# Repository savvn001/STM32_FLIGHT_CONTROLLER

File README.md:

# STM32_FLIGHT_CONTROLLER

(Still undergoing active development)

Open source flight controller running on an STM32F411RE MCU and a custom designed PCB. Project written in STM32cubeIDE. 

The other modules this flight controller currently uses:

- NRF24L01PA for RF comms
- GPS is provided by a uBlox NEO6M GPS module
- Orientation from an MPU9250 9-axis IMU.

Current features:
- User control
- Packetised RF communications
- GPS 
- In flight monitoring of telemetry information (battery level, orientation, GPS co-ordinates etc.)
- More to come!

The first revision of the flight controller designed in eagle is shown below.

The controller features headers for I2C, 4 GPIO pins, UART and an NRF24L01 module. The code for the associated user controller/transmitter is here: https://github.com/savvn001/DRONE_CONTROLLER_F4746NG

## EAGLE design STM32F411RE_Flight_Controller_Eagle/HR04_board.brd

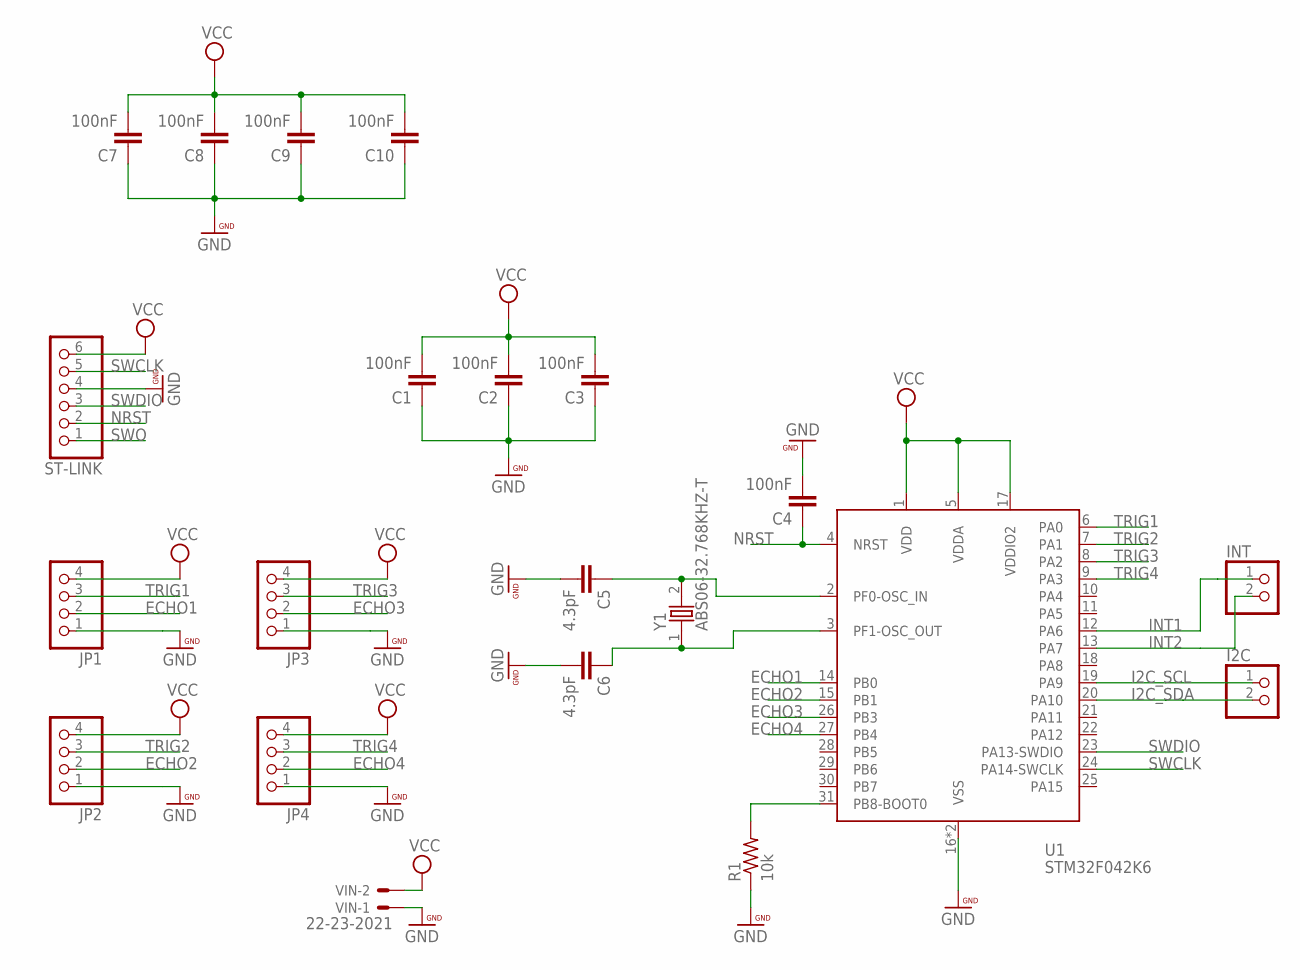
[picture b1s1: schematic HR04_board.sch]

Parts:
C1, C2, C3, C4, C7, C8, C9, C10: 100nF; 0603-CAP
C5, C6: 4.3pF; 0402-CAP
I2C: PINHD-1X2; 1X02
INT: PINHD-1X2; 1X02
JP1, JP2, JP3, JP4: PINHD-1X4; 1X04
R1: 10k; R0603
ST-LINK: PINHD-1X6; 1X06
U1: STM32F042K6; QFP32-7X7
VIN: 22-23-2021
Y1: ABS06-32.768KHZ-T; XTAL_ABS06-32.768KHZ-T

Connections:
ECHO1: JP1.2, U1.14 (PB0)
ECHO2: JP2.2, U1.15 (PB1)
ECHO3: JP3.2, U1.26 (PB3)
ECHO4: JP4.2, U1.27 (PB4)
GND: C1.1, C2.1, C3.1, C4.2, C5.2, C6.2, C7.1, C8.1, C9.1, C10.1, JP1.1, JP2.1, JP3.1, JP4.1, R1.1, ST-LINK.4, U1.16 (VSS), U1.32 (VSS), VIN.1
I2C_SCL: I2C.1, U1.19 (PA9)
I2C_SDA: I2C.2, U1.20 (PA10)
INT1: INT.1, U1.12 (PA6)
INT2: INT.2, U1.13 (PA7)
unnamed: R1.2, U1.31 (PB8-BOOT0)
unnamed: C5.1, U1.2 (PF0-OSC_IN), Y1.2
unnamed: C6.1, U1.3 (PF1-OSC_OUT), Y1.1
NRST: C4.1, ST-LINK.2, U1.4 (NRST)
SWCLK: ST-LINK.5, U1.24 (PA14-SWCLK)
SWDIO: ST-LINK.3, U1.23 (PA13-SWDIO)
SWO: ST-LINK.1
TRIG1: JP1.3, U1.6 (PA0)
TRIG2: JP2.3, U1.7 (PA1)
TRIG3: JP3.3, U1.8 (PA2)
TRIG4: JP4.3, U1.9 (PA3)
VCC: C1.2, C2.2, C3.2, C7.2, C8.2, C9.2, C10.2, JP1.4, JP2.4, JP3.4, JP4.4, ST-LINK.6, U1.1 (VDD), U1.5 (VDDA), U1.17 (VDDIO2), VIN.2

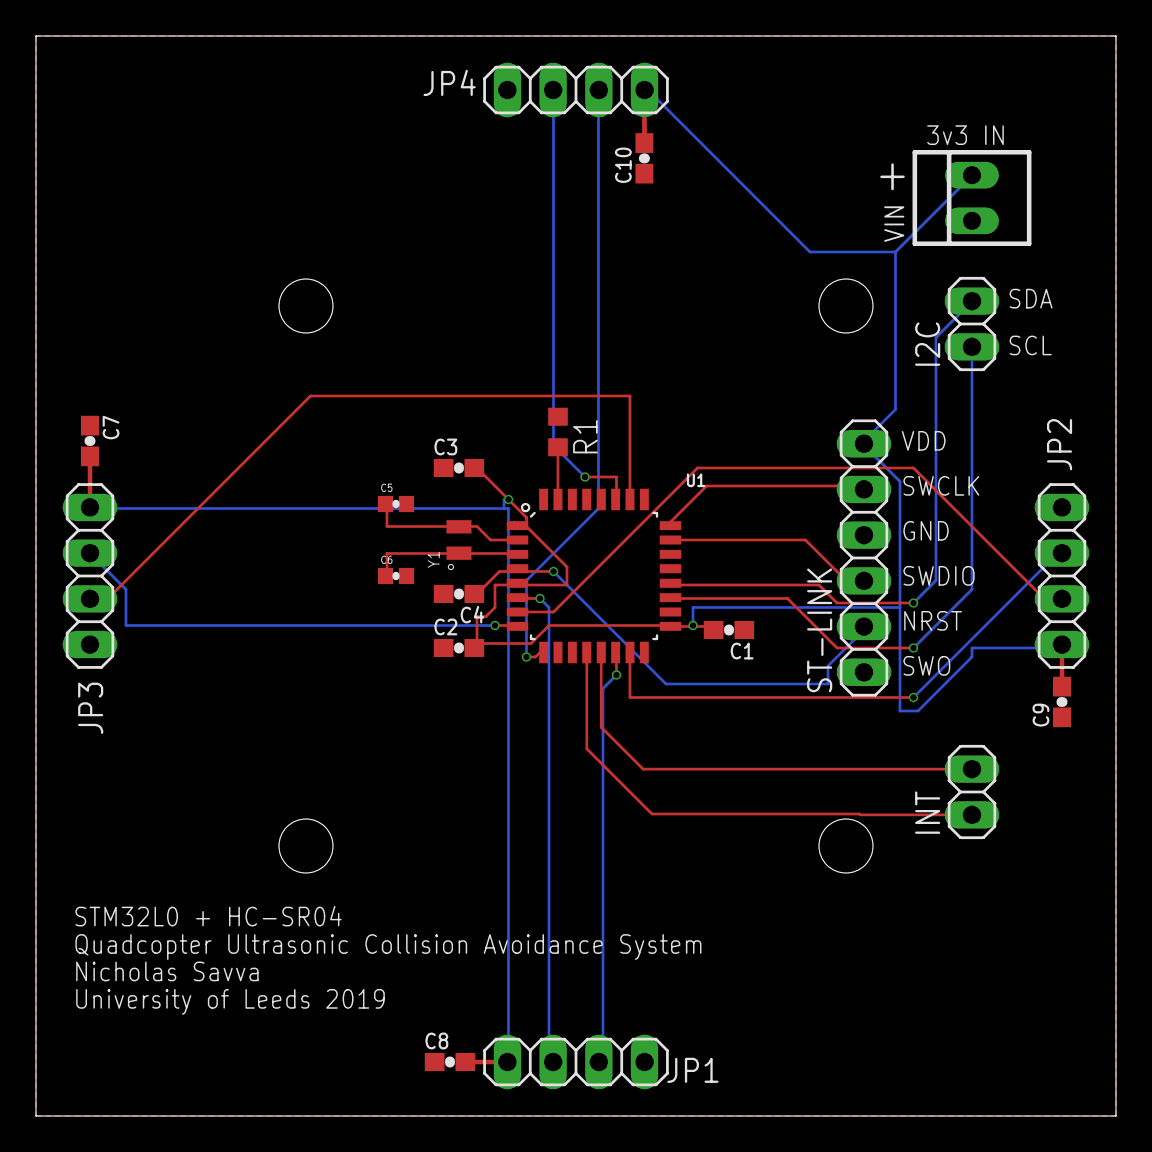
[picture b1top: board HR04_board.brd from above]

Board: 2 copper layers, 60.0 x 60.0 mm, 21 parts (0 on the bottom side), 20 nets.

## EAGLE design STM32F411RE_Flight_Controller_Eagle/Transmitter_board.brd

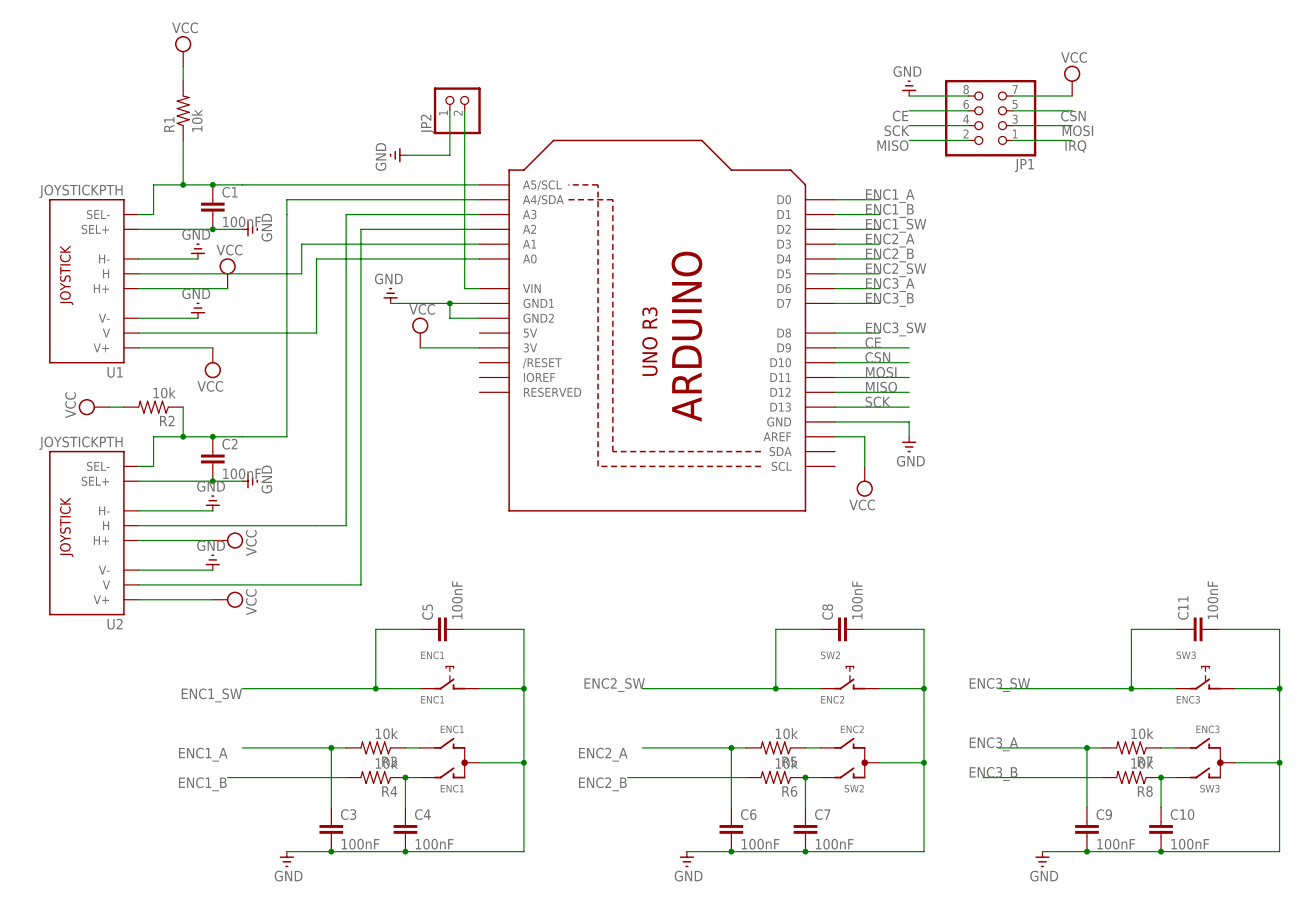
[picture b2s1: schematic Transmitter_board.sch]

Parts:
C1, C2, C3, C4, C5, C6, C7, C8, C9, C10, C11: 100nF; 0603-CAP
ENC1: ENC1; ALPS_EC12E_SW
JP1: PINHD-2X4; 2X04
JP2: PINHD-1X2; 1X02
R1, R2, R3, R4, R5, R6, R7, R8: 10k; 0603-RES
SW2: ENC2; ALPS_EC12E_SW
SW3: ENC3; ALPS_EC12E_SW
U1, U2: JOYSTICKPTH; JOYSTICK
U3: STM32F746NG; ARDUINOR3-BPLACE

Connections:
5V: U3.5V
CE: JP1.6, U3.D9
CSN: JP1.5, U3.D10
ENC1_A: C3.1, R3.2, U3.D0
ENC1_B: R4.2, U3.D1
ENC1_SW: C5.1, ENC1.E (2), U3.D2
ENC2_A: C6.1, R5.2, U3.D3
ENC2_B: R6.2, U3.D4
ENC2_SW: C8.1, SW2.E (2), U3.D5
ENC3_A: C9.1, R7.2, U3.D6
ENC3_B: R8.2, U3.D7
ENC3_SW: C11.1, SW3.E (2), U3.D8
GND: C1.2, C2.2, C3.2, C4.2, C5.2, C6.2, C7.2, C8.2, C9.2, C10.2, C11.2, ENC1.C, ENC1.D (1), JP1.8, JP2.1, SW2.C, SW2.D (1), SW3.C, SW3.D (1), U1.B1A (SEL+), U1.H3 (H-), U1.V3 (V-), U2.B1A (SEL+), U2.H3 (H-), U2.V3 (V-), U3.GND, U3.GND1, U3.GND2
IRQ: JP1.1
MISO: JP1.2, U3.D12
MOSI: JP1.3, U3.D11
unnamed: U2.V2 (V), U3.A2
unnamed: C2.1, R2.1, U2.B2A (SEL-), U3.A4 (A4/SDA)
unnamed: JP2.2, U3.VIN
unnamed: C1.1, R1.1, U1.B2A (SEL-), U3.A5 (A5/SCL)
unnamed: C4.1, ENC1.A, R4.1
unnamed: C7.1, R6.1, SW2.A
unnamed: ENC1.B, R3.1
unnamed: R5.1, SW2.B
unnamed: C10.1, R8.1, SW3.A
unnamed: R7.1, SW3.B
unnamed: U1.H2 (H), U3.A1
unnamed: U1.V2 (V), U3.A0
unnamed: U2.H2 (H), U3.A3
SCK: JP1.4, U3.D13
VCC: JP1.7, R1.2, R2.2, U1.H1 (H+), U1.V1 (V+), U2.H1 (H+), U2.V1 (V+), U3.3V, U3.AREF

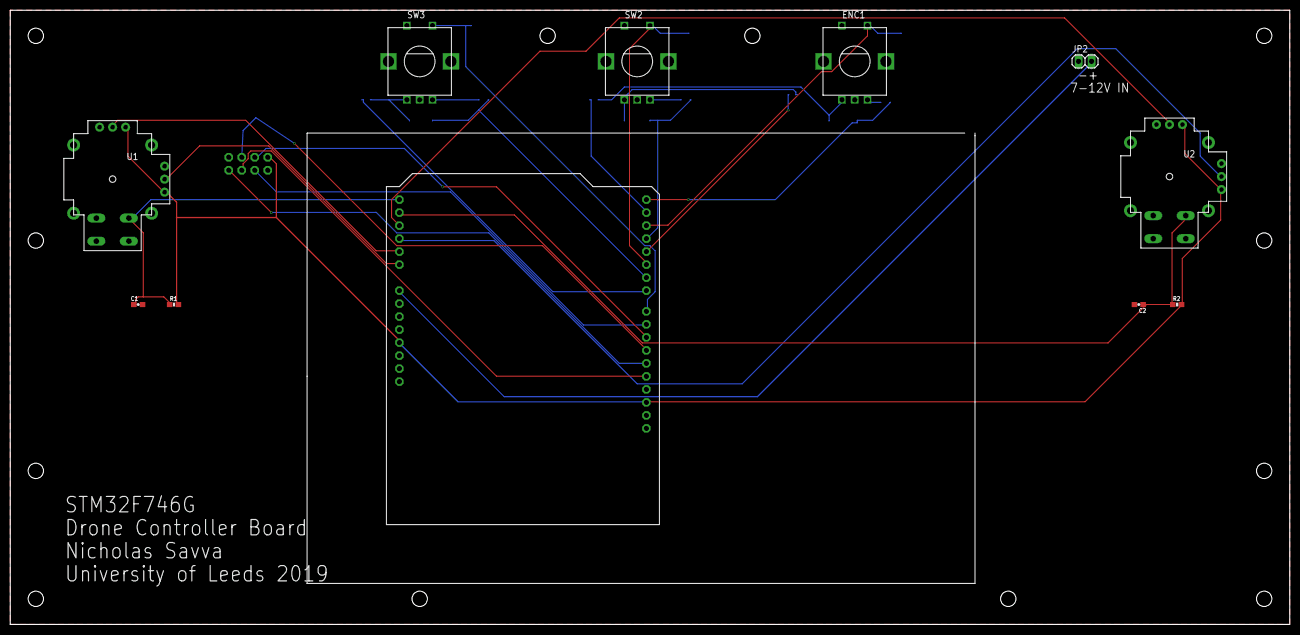
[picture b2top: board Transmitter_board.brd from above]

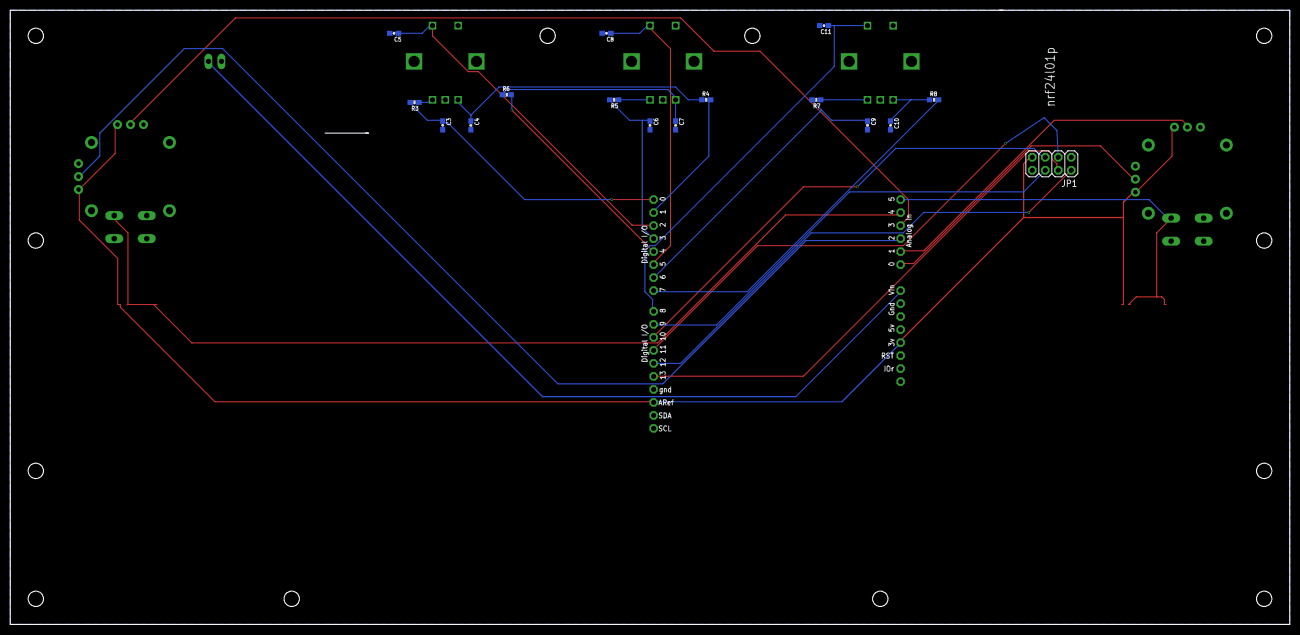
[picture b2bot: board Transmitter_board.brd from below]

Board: 2 copper layers, 250.0 x 120.0 mm, 27 parts (17 on the bottom side), 29 nets.

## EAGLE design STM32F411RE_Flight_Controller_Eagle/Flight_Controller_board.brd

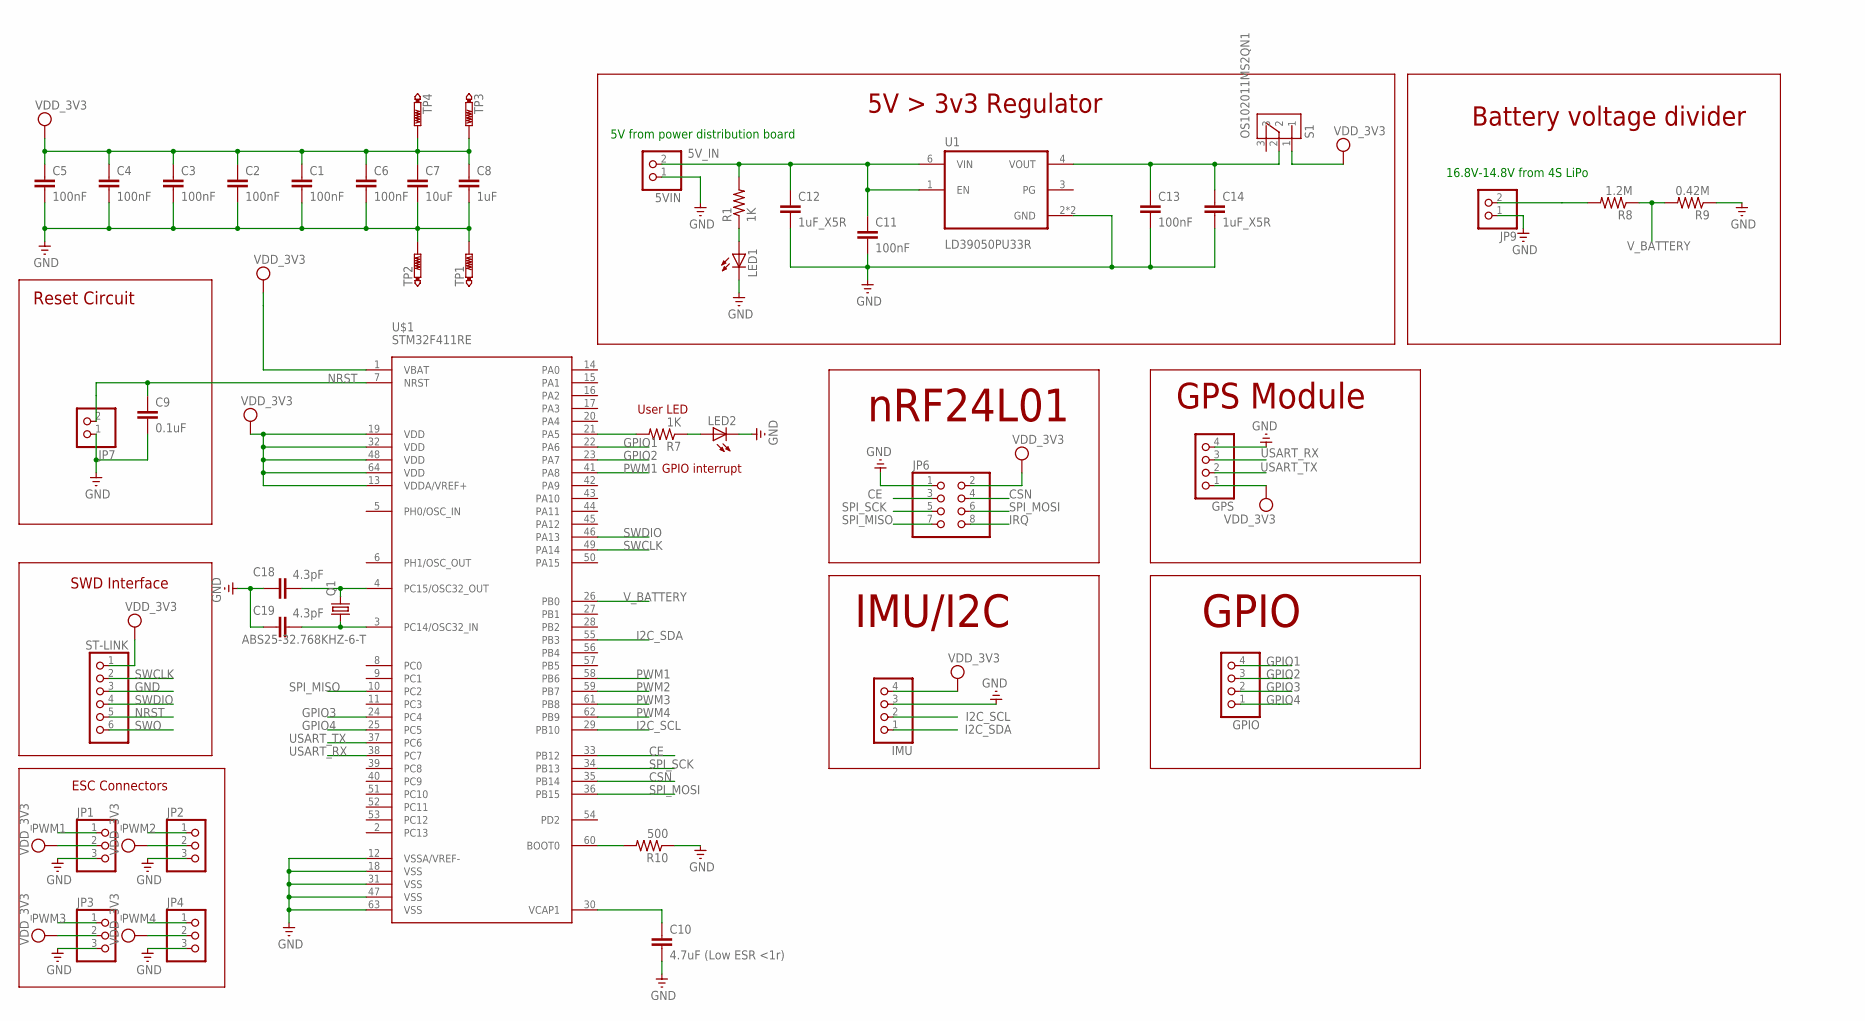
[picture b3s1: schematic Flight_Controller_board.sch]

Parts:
5VIN: PINHD-1X2; 1X02
C1, C2, C3, C4, C5, C6, C11, C13: 100nF; 0603-CAP
C7: 10uF; 0603-CAP
C8: 1uF; 0603-CAP
C9: 0.1uF; 0603-CAP
C10: 4.7uF (Low ESR <1r); 1210
C12, C14: 1uF_X5R; 0603-CAP
C18, C19: 4.3pF; 0603-CAP
GPIO: PINHD-1X4; 1X04
GPS: PINHD-1X4; 1X04
IMU: PINHD-1X4; 1X04
JP1, JP2, JP3, JP4: PINHD-1X3; 1X03
JP6: PINHD-2X4; 2X04
JP7, JP9: PINHD-1X2; 1X02
LED1, LED2: LEDCHIPLED_0603; CHIPLED_0603
Q1: ABS25-32.768KHZ-6-T; MC-306
R1, R7: 1K; 0603-RES
R8: 1.2M; 0603-RES
R9: 0.42M; 0603-RES
R10: 500; 0603-RES
S1: OS102011MS2QN1; SW_OS102011MS2QN1
ST-LINK: PINHD-1X6; 1X06
TP1, TP2, TP3, TP4: PTR1B1,27; B1,27
U1: LD39050PU33R; SON95P300X300X100-7N
U$1: STM32F411RE; LQFP64

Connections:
5V_IN: 5VIN.2, C11.1, C12.1, R1.2, U1.1 (EN), U1.6 (VIN)
CE: JP6.3, U$1.33 (PB12)
CSN: JP6.4, U$1.35 (PB14)
GND: 5VIN.1, C1.2, C2.2, C3.2, C4.2, C5.2, C6.2, C7.2, C8.2, C9.2, C10.2, C11.2, C12.2, C13.2, C14.2, C18.1, C19.1, GPS.4, IMU.3, JP1.3, JP2.3, JP3.3, JP4.3, JP6.1, JP7.1, JP9.1, LED1.C, LED2.C, R9.1, R10.1, ST-LINK.3, TP1.TP, TP2.TP, U1.2 (GND), U1.7 (GND), U$1.12 (VSSA/VREF-), U$1.18 (VSS), U$1.31 (VSS), U$1.47 (VSS), U$1.63 (VSS)
GPIO1: GPIO.4, U$1.22 (PA6)
GPIO2: GPIO.3, U$1.23 (PA7)
GPIO3: GPIO.2, U$1.24 (PC4)
GPIO4: GPIO.1, U$1.25 (PC5)
I2C_SCL: IMU.2, U$1.29 (PB10)
I2C_SDA: IMU.1, U$1.55 (PB3)
IRQ: JP6.8
unnamed: C10.1, U$1.30 (VCAP1)
unnamed: C13.1, C14.1, S1.2, U1.4 (VOUT)
unnamed: R7.2, U$1.21 (PA5)
unnamed: LED1.A, R1.1
unnamed: LED2.A, R7.1
unnamed: C18.2, Q1.4 (2), U$1.4 (PC15/OSC32_OUT)
unnamed: C19.2, Q1.1, U$1.3 (PC14/OSC32_IN)
unnamed: JP9.2, R8.2
unnamed: R10.2, U$1.60 (BOOT0)
NRST: C9.1, JP7.2, ST-LINK.5, U$1.7 (NRST)
PWM1: JP1.1, U$1.41 (PA8), U$1.58 (PB6)
PWM2: JP2.1, U$1.59 (PB7)
PWM3: JP3.1, U$1.61 (PB8)
PWM4: JP4.1, U$1.62 (PB9)
SPI_MISO: JP6.7, U$1.10 (PC2)
SPI_MOSI: JP6.6, U$1.36 (PB15)
SPI_SCK: JP6.5, U$1.34 (PB13)
SWCLK: ST-LINK.2, U$1.49 (PA14)
SWDIO: ST-LINK.4, U$1.46 (PA13)
SWO: ST-LINK.6
USART_RX: GPS.3, U$1.38 (PC7)
USART_TX: GPS.2, U$1.37 (PC6)
VDD: C1.1, C2.1, C3.1, C4.1, C5.1, C6.1, C7.1, C8.1, GPS.1, IMU.4, JP1.2, JP2.2, JP3.2, JP4.2, JP6.2, S1.1, ST-LINK.1, TP3.TP, TP4.TP, U$1.1 (VBAT), U$1.13 (VDDA/VREF+), U$1.19 (VDD), U$1.32 (VDD), U$1.48 (VDD), U$1.64 (VDD)
V_BATTERY: R8.1, R9.2, U$1.26 (PB0)

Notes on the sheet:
Reset Circuit
SWD Interface
ESC Connectors
5V > 3v3 Regulator
nRF24L01
GPS Module
16.8V-14.8V from 4S LiPo
Battery voltage divider
GPIO interrupt
User LED
5V from power distribution board
IMU/I2C
GPIO

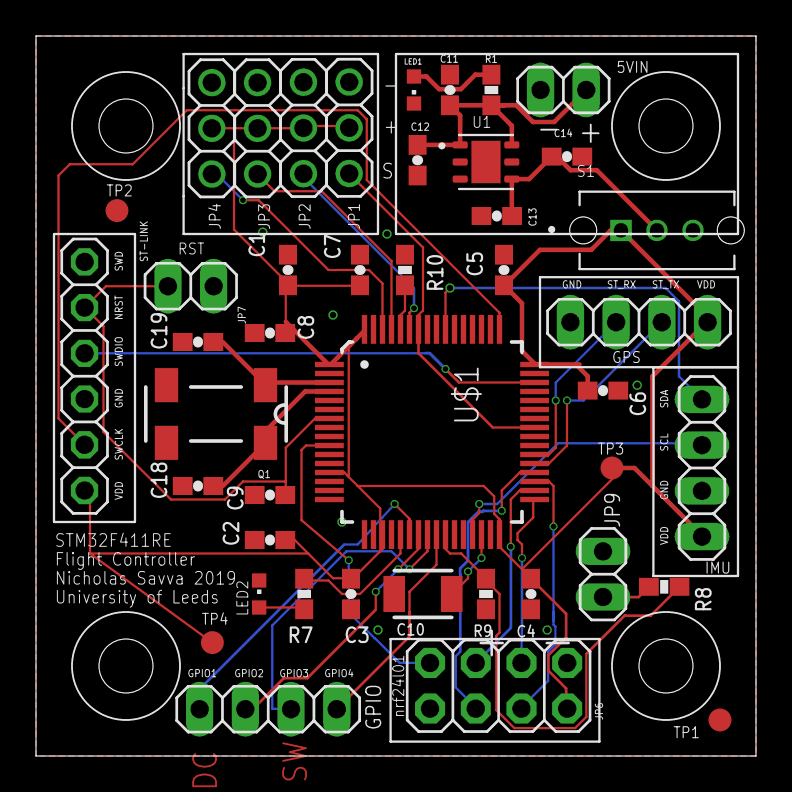
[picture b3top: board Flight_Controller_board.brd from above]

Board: 2 copper layers, 40.0 x 40.0 mm, 43 parts (0 on the bottom side), 33 nets.

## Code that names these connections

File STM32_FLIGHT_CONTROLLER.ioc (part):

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Mcu.Name=STM32F411R(C-E)Tx
Mcu.Package=LQFP64
Mcu.UserName=STM32F411RETx
PA13.Mode=Serial_Wire
PA13.Signal=SYS_JTMS-SWDIO
PA14.Mode=Serial_Wire
PA14.Signal=SYS_JTCK-SWCLK
PA5.Signal=GPIO_Output
PA8.GPIOParameters=GPIO_PuPd,GPIO_Label,GPIO_ModeDefaultEXTI
PA8.GPIO_Label=PWM_INT
PA8.GPIO_ModeDefaultEXTI=GPIO_MODE_IT_RISING
PA8.GPIO_PuPd=GPIO_NOPULL
PA8.Signal=GPXTI8
PB10.GPIOParameters=GPIO_Speed,GPIO_PuPdOD,GPIO_Mode
PB10.GPIO_Mode=GPIO_MODE_AF_OD
PB10.GPIO_PuPdOD=GPIO_PULLUP
PB10.GPIO_Speed=GPIO_SPEED_FREQ_VERY_HIGH
PB10.Mode=I2C
PB10.Signal=I2C2_SCL
PB12.GPIOParameters=GPIO_Speed,PinState,GPIO_PuPd,GPIO_ModeDefaultOutputPP
PB12.GPIO_ModeDefaultOutputPP=GPIO_MODE_OUTPUT_PP
PB12.GPIO_PuPd=GPIO_NOPULL
PB12.GPIO_Speed=GPIO_SPEED_FREQ_HIGH
PB12.PinState=GPIO_PIN_RESET
PB12.Signal=GPIO_Output
PB13.Mode=Full_Duplex_Master
PB13.Signal=SPI2_SCK
PB14.GPIOParameters=GPIO_Speed,PinState,GPIO_PuPd,GPIO_ModeDefaultOutputPP
PB14.GPIO_ModeDefaultOutputPP=GPIO_MODE_OUTPUT_PP
PB14.GPIO_PuPd=GPIO_NOPULL
PB14.GPIO_Speed=GPIO_SPEED_FREQ_HIGH
PB14.PinState=GPIO_PIN_RESET
PB14.Signal=GPIO_Output
PB15.Mode=Full_Duplex_Master
PB15.Signal=SPI2_MOSI
PB3.GPIOParameters=GPIO_Speed,GPIO_PuPdOD,GPIO_Mode
PB3.GPIO_Mode=GPIO_MODE_AF_OD
PB3.GPIO_PuPdOD=GPIO_PULLUP
PB3.GPIO_Speed=GPIO_SPEED_FREQ_VERY_HIGH
PB3.Mode=I2C
PB3.Signal=I2C2_SDA
PB6.GPIOParameters=GPIO_ModeDefaultPP,GPIO_Speed,GPIO_PuPd
PB6.GPIO_ModeDefaultPP=GPIO_MODE_AF_PP
PB6.GPIO_PuPd=GPIO_NOPULL
PB6.GPIO_Speed=GPIO_SPEED_FREQ_LOW
PB6.Signal=S_TIM4_CH1
PB7.GPIOParameters=GPIO_ModeDefaultPP,GPIO_Speed,GPIO_PuPd
PB7.GPIO_ModeDefaultPP=GPIO_MODE_AF_PP
PB7.GPIO_PuPd=GPIO_NOPULL
PB7.GPIO_Speed=GPIO_SPEED_FREQ_LOW
PB7.Signal=S_TIM4_CH2
PB8.GPIOParameters=GPIO_ModeDefaultPP,GPIO_Speed,GPIO_PuPd
PB8.GPIO_ModeDefaultPP=GPIO_MODE_AF_PP
PB8.GPIO_PuPd=GPIO_NOPULL
PB8.GPIO_Speed=GPIO_SPEED_FREQ_LOW
PB8.Signal=S_TIM4_CH3
PB9.Signal=S_TIM4_CH4
PC2.Mode=Full_Duplex_Master
PC2.Signal=SPI2_MISO
PC5.GPIOParameters=GPIO_Speed,PinState,GPIO_PuPd,GPIO_ModeDefaultOutputPP
PC5.GPIO_ModeDefaultOutputPP=GPIO_MODE_OUTPUT_PP
PC5.GPIO_PuPd=GPIO_NOPULL
PC5.GPIO_Speed=GPIO_SPEED_FREQ_HIGH
PC5.PinState=GPIO_PIN_RESET
PC5.Signal=GPIO_Output
PC6.Mode=Asynchronous
PC6.Signal=USART6_TX
PC7.Mode=Asynchronous
PC7.Signal=USART6_RX
RCC.HSE_VALUE=8000000
RCC.SYSCLKFreq_VALUE=100000000
RCC.SYSCLKSource=RCC_SYSCLKSOURCE_PLLCLK
board=NUCLEO-F411RE
boardIOC=true

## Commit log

2019-06-25 Added foo to the bar
2019-07-08 Before adding DSP instructions
2019-07-10 Minor Bugfixes
    Minor fixes to do with control loop.
    PWM freq upped to 2khz but still at 500hz refresh rate.
2019-07-13 Minor fixes
2019-07-19 Working PID control at 505hz
    Working PID control at 505hz, gains need tuning
2019-07-26 Added NRF24 module libs
    Added NRF24 module libs and implemented basic Rx functionality receiving from STM32F7 board
2019-07-26 Working Joystick Position Tx
2019-07-29 Working Tx-Rx with Ack payload
2019-08-01 TIM3 Reconfigured for DMA UART Timeout detection
2019-08-08 Working throttle control
2019-08-09 Added ADC for battery level
2019-08-14 Bugfixes
2019-08-20 Formatting, minor fixes
2019-08-23 Few failsafes
2019-09-06 Copied files for eMD library, not yet implemented
2019-09-07 Working DMP (needs bias adjustment)
2019-09-08 DMP but with yaw drift
2019-09-08 Re-ported DMP library
2019-09-09 Added Eagle project files
2019-09-09 Pics
2019-09-13 I2C replaced with non blocking DMA
2019-09-21 freeRTOS
2019-09-21 Fixed sys
2019-09-22 GPS parsing redone
    Using UART Idle line detection interrupt to self time out without using timer like before (Note: have to copy over again HAL_UART.c and .h files if cubeMX is regenerated as have implemented a small h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
2019-09-22 Ack payload 1 re packeted
2019-09-23 Fixed NRF24 connection with RTOS
2019-09-23 test
2019-09-24 re calibrated mag
2019-09-25 fixed yaw ctrl
2019-10-16 PID values received externally from Tx
2019-10-16 Commit due to clash
2019-10-29 Fixed NRF Tx/Rx Delay
2019-10-29 I2C with IT

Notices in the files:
parts and their libraries:
PatternAgents-ProtoPads: License : http://creativecommons.org/licenses/by-sa/4.0
(Creative Commons 4.0)
PatternAgents-Beautify: License : http://creativecommons.org/licenses/by-sa/3.0
(Creative Commons 3.0)
